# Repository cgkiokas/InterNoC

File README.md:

# InterNoC
InterNoC prototype board

### Description:
Nowadays, many embedded systems host a significant number of micro-controllers and processors (i.e. IoT devices, vehicles, airplanes, satellites) and as this number continues to increase, traditional bus solutions will start to fail on those platforms as well. Network-on-Chip (NoC) not only offer a scalable solution for MPSoC interconnects but they can also provide a uniform platform of communication to embedded systems with multiple interconnected devices.

This project aims to build an open-source FPGA-based NoC where devices can be connected to each other, transparently, enabling mixed protocol communication between multiple master / slave devices, without the need for a shared bus and at the same time allowing each device to operate in its own clock domain.

### Link to project page:
https://hackaday.io/project/27083-internoc

### Setup Notes:
All components are packed in InterNoC.lib & InterNoC.pretty so adding them in the component library and putting it in top priority should make the parts fully portable.

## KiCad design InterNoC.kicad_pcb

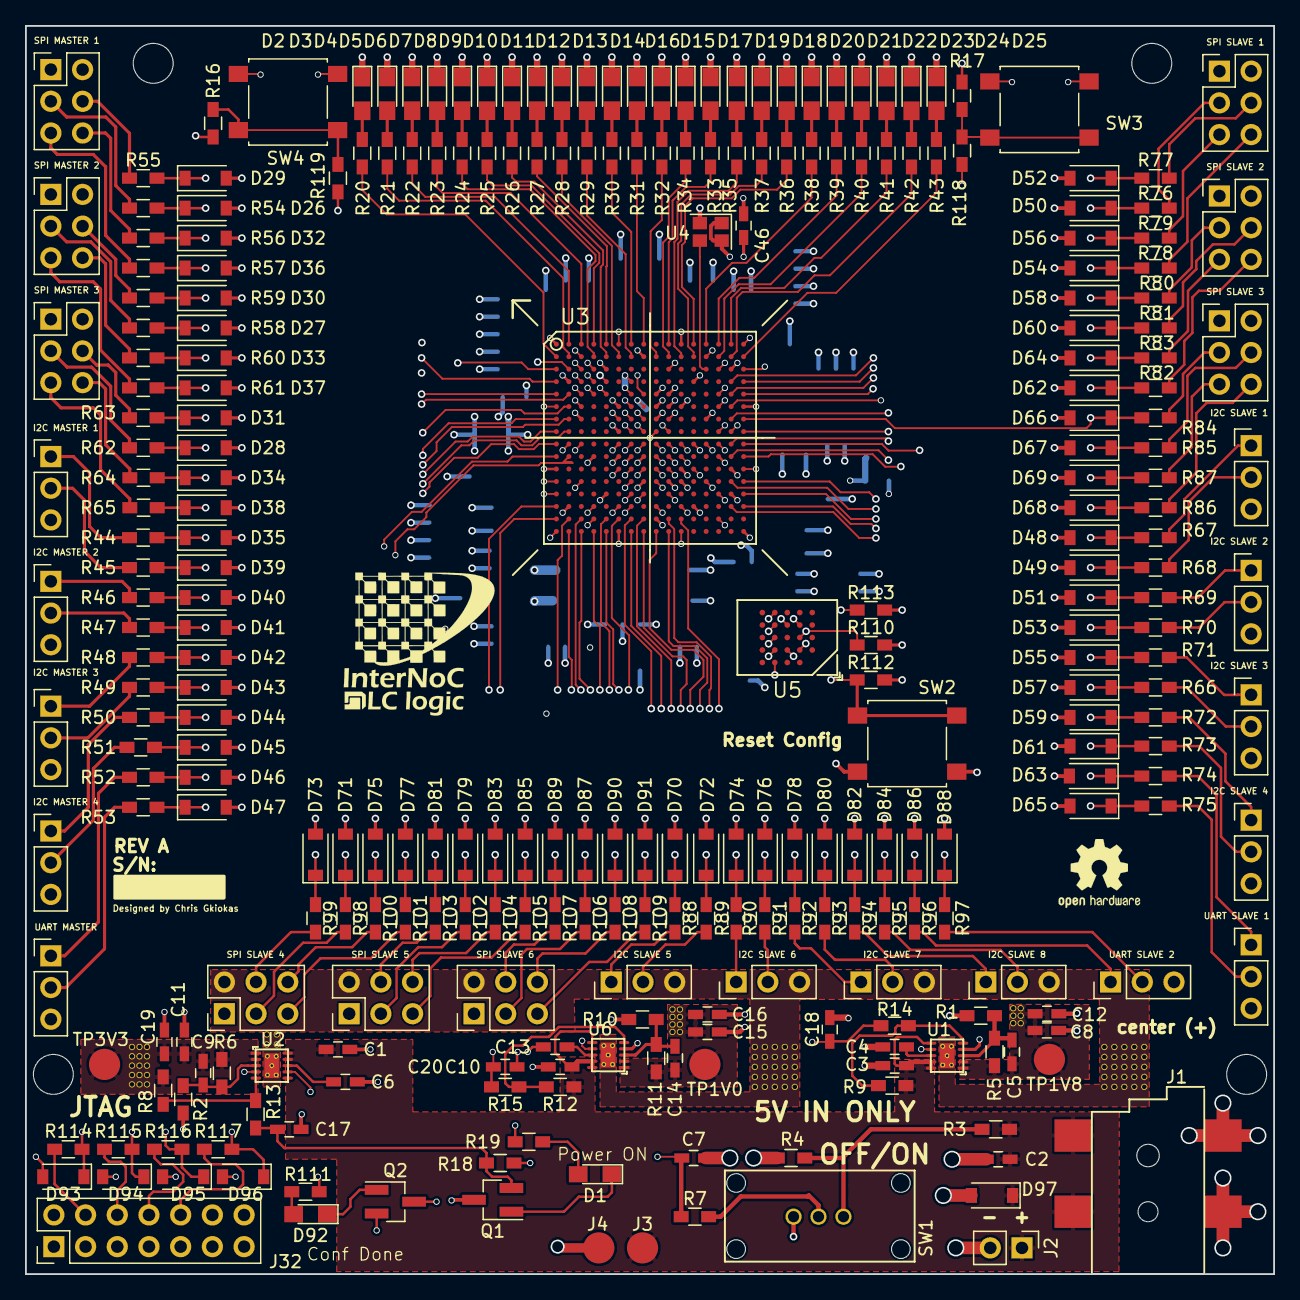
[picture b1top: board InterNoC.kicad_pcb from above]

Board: 6 copper layers, 100.0 x 100.0 mm, 345 parts (0 on the bottom side), 226 nets.

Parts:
C1, C3, C8, C10, C11, C15: 10uF X5R; C_0603_HandSoldering
C2: 10uF; C_0603_HandSoldering
C4, C6, C13: 0.1uF; C_0603_HandSoldering
C5, C9, C14, C114: 10nF X5R; C_0603_HandSoldering
C7, C46, C110: 100nF; C_0603_HandSoldering
C12, C16, C19: 100nF X5R; C_0603_HandSoldering
C17: 220nF; C_0603_HandSoldering
C18, C20: 680nF; C_0603_HandSoldering
C21, C22, C23, C24, C80: 100uF X5R; C_1210_HandSoldering
C25, C26, C27, C28, C29, C30, C31, C32, C83, C87, C91, C94: 4.7uF X5R; C_0805_HandSoldering
C33, C34, C35, C36, C37, C38, C39, C40, C41, C42, C43, C44, C45, C47, C48, C49, C85, C92, C95, C97, C98, C100, C104, C109: 470nF X5R; C_0603_HandSoldering
C50, C51, C52, C53, C54, C55, C56, C57, C89, C101, C105, C106, C108, C111, C113: 47nF X5R; C_0603_HandSoldering
C81, C86: 47uF X5R; C_1210_HandSoldering
C107: 47uF; C_1210_HandSoldering
C112: 470nF; C_0603_HandSoldering
D1, D2, D3, D4, D5, D6, D7, D8, D9, D10, D11, D12, D13, D14, D15, D16, D17, D18, D19, D20, D21, D22, D23, D24, D25, D92: LED; LED_0805_HandSoldering
D26, D27, D28, D29, D30, D31, D32, D33, D34, D35, D36, D37, D38, D39, D40, D41, D42, D43, D44, D45, D46, D47, D48, D49, D50, D51, D52, D53, D54, D55, D56, D57, D58, D59, D60, D61, D62, D63, D64, D65, D66, D67, D68, D69, D70, D71, D72, D73, D74, D75, D76, D77, D78, D79, D80, D81, D82, D83, D84, D85, D86, D87, D88, D89, D90, D91, D93, D94, D95, D96: 3.3v; D_SOD-123
D97: 6v; D_SOD-123
I2C MASTER 1: I2C_MASTER_1; Pin_Header_Straight_1x03_Pitch2.54mm
I2C MASTER 2: I2C_MASTER_2; Pin_Header_Straight_1x03_Pitch2.54mm
I2C MASTER 3: I2C_MASTER_3; Pin_Header_Straight_1x03_Pitch2.54mm
I2C MASTER 4: I2C_MASTER_4; Pin_Header_Straight_1x03_Pitch2.54mm
I2C SLAVE 1: I2C_SLAVE_1; Pin_Header_Straight_1x03_Pitch2.54mm
I2C SLAVE 2: I2C_SLAVE_2; Pin_Header_Straight_1x03_Pitch2.54mm
I2C SLAVE 3: I2C_SLAVE_3; Pin_Header_Straight_1x03_Pitch2.54mm
I2C SLAVE 4: I2C_SLAVE_4; Pin_Header_Straight_1x03_Pitch2.54mm
I2C SLAVE 5: I2C_SLAVE_5; Pin_Header_Straight_1x03_Pitch2.54mm
I2C SLAVE 6: I2C_SLAVE_6; Pin_Header_Straight_1x03_Pitch2.54mm
I2C SLAVE 7: I2C_SLAVE_7; Pin_Header_Straight_1x03_Pitch2.54mm
I2C SLAVE 8: I2C_SLAVE_8; Pin_Header_Straight_1x03_Pitch2.54mm
J1: BARREL_JACK; PJ-002AH-SMT-TR
J2: CONN_01X02; Pin_Header_Straight_1x02_Pitch2.54mm
J3: TEST_PW_IN; test_point_single
J4: TEST_GND; test_point_single
J32: JTAG HEADER; Pin_Header_Straight_2x07_Pitch2.54mm
L4, L5: 600Ohm/100Mhz; L_0805_HandSoldering
Q1: FDV301N; SOT-23_Handsoldering
Q2: Q_NMOS_DGS; SOT-23_Handsoldering
R1: 1.5K 1%; R_0603_HandSoldering
R2: 1.15K 1%; R_0603_HandSoldering
R3, R4, R7, R16, R17, R18, R118, R119: 10K; R_0603_HandSoldering
R5: 1.87K 1%; R_0603_HandSoldering
R6: 3.57K 1%; R_0603_HandSoldering
R8: 20K; R_0603_HandSoldering
R9, R12: 56K; R_0603_HandSoldering
R10: 10.2K 1%; R_0603_HandSoldering
R11: 2.55K 1%; R_0603_HandSoldering
R13, R14, R15: 4.7K; R_0603_HandSoldering
R19: 680R; R_0603_HandSoldering
R20, R21, R22, R23, R24, R25, R26, R27, R28, R29, R30, R31, R32, R33, R34, R35, R36, R37, R38, R39, R40, R41, R42, R43, R111: 330R; R_0603_HandSoldering
R44, R45, R46, R47, R48, R49, R50, R51, R52, R53, R54, R55, R56, R57, R58, R59, R60, R61, R62, R63, R64, R65, R66, R67, R68, R69, R70, R71, R72, R73, R74, R75, R76, R77, R78, R79, R80, R81, R82, R83, R84, R85, R86, R87, R88, R89, R90, R91, R92, R93, R94, R95, R96, R97, R98, R99, R100, R101, R102, R103, R104, R105, R106, R107, R108, R109, R114, R115, R116, R117: 200; R_0603_HandSoldering
R110, R112, R113: 4.7k; R_0603_HandSoldering
SPI MASTER 1: SPI_MASTER_1; Pin_Header_Straight_2x03_Pitch2.54mm
SPI MASTER 2: SPI_MASTER_2; Pin_Header_Straight_2x03_Pitch2.54mm
SPI MASTER 3: SPI_MASTER_3; Pin_Header_Straight_2x03_Pitch2.54mm
SPI SLAVE 1: SPI_SLAVE_1; Pin_Header_Straight_2x03_Pitch2.54mm
SPI SLAVE 2 : SPI_SLAVE_2; Pin_Header_Straight_2x03_Pitch2.54mm
SPI SLAVE 3: SPI_SLAVE_3; Pin_Header_Straight_2x03_Pitch2.54mm
SPI SLAVE 4: SPI_SLAVE_4; Pin_Header_Straight_2x03_Pitch2.54mm
SPI SLAVE 5: SPI_SLAVE_5; Pin_Header_Straight_2x03_Pitch2.54mm
SPI SLAVE 6: SPI_SLAVE_6; Pin_Header_Straight_2x03_Pitch2.54mm
SW1: SW_SPDT; MSS120004
SW2: RST_CONF; SW_SPST_B3S-1000
SW3, SW4: SW_Push; SW_SPST_B3S-1000
TP1V0: TEST_1V0; test_point_single
TP1V8: TEST_1V8; test_point_single
TP3V3: TEST_3V3; test_point_single
U1, U6: TPS7A9101DSKT
U2: TPS7A9201DSKR
U3: xc7a35tftg256; XC7A35T-1FTG256C
U4: ABRACON_ASDM1-100.000MHZ-LC-T; Crystal_SMD_2520-4pin_2.5x2.0mm
U5: S25FL128SAGBHIA00
UART MASTER : UART_MASTER_1; Pin_Header_Straight_1x03_Pitch2.54mm
UART SLAVE 1: UART_SLAVE_1; Pin_Header_Straight_1x03_Pitch2.54mm
UART SLAVE 2: UART_SLAVE_2; Pin_Header_Straight_1x03_Pitch2.54mm

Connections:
/Artix7/GNDADC: C114.2, L5.1, U3.G7, U3.H7, U3.H8, U3.J7, U3.J8
/Artix7/TCK: D94.1, R115.2, U3.L7
/Artix7/TDI: D96.1, R117.2, U3.N7
/Artix7/TDO: D95.1, R116.2, U3.N8
/Artix7/TMS: D93.1, R114.2, U3.M7
/Artix7/VCC1V0: C14.1, C15.1, C16.1, C80.1, C83.1, C87.1, C92.1, C95.1, C98.1, C101.1, C105.1, C107.1, C108.1, C112.1, C113.1, R11.1, TP1V0.1, U3.E10, U3.F7, U3.F9, U3.F11, U3.G6, U3.H9, U3.J6, U3.K9, U3.L8, U6.1, U6.2
/Artix7/VCC1V8: C5.1, C8.1, C12.1, C86.1, C91.1, C94.1, C97.1, C100.1, C104.1, C106.1, C111.1, L4.2, R5.1, TP1V8.1, U1.1, U1.2, U3.F8, U3.G10, U3.J10, U3.K11, U3.L10
/Artix7/VCC3V3: C9.1, C11.1, C19.1, C21.1, C22.1, C23.1, C24.1, C25.1, C26.1, C27.1, C28.1, C29.1, C30.1, C31.1, C32.1, C33.1, C34.1, C35.1, C36.1, C37.1, C38.1, C39.1, C40.1, C41.1, C42.1, C43.1, C44.1, C45.1, C46.1, C47.1, C48.1, C49.1, C50.1, C51.1, C52.1, C53.1, C54.1, C55.1, C56.1, C57.1, C81.1, C85.1, C89.1, C110.1, J32.2, R6.1, R8.2, R18.2, R19.2, R110.1, R111.1, R112.1, R113.1, SW3.1, SW4.1, TP3V3.1, U2.1, U2.2, U3.A6, U3.A16, U3.B3, U3.B13, U3.C10, U3.D7, U3.E4, U3.E7, U3.E14, U3.F1, U3.H15, U3.J2, U3.J12, U3.L6, U3.L16, U3.M3, U3.M9, U3.M13, U3.N10, U3.P7, U3.R4, U3.R14, U3.T1, U3.T11, U4.1, U4.4, U5.A4, U5.B4, U5.C4, U5.D4, U5.E4
/Artix7/VCCADC: C109.1, C114.1, L4.1, U3.G8
/PowerSupply/PGOOD: C17.1, Q1.2, R13.2, R18.1
/PowerSupply/PGOOD1V0: C20.1, R15.2, U1.7
/PowerSupply/PGOOD1V8: C18.1, R14.2, U2.7
/PowerSupply/PWR_IN: C1.1, C2.1, C3.1, C10.1, D97.1, J1.1, J2.1, J3.1, R3.1, R9.2, R12.2, U1.6, U1.9, U1.10, U2.6, U2.9, U2.10, U6.6, U6.9, U6.10
CLOCK: U3.C13, U4.3
GND: C1.2, C2.2, C3.2, C4.2, C6.2, C7.2, C8.2, C10.2, C11.2, C12.2, C13.2, C15.2, C16.2, C17.2, C18.2, C19.2, C20.2, C21.2, C22.2, C23.2, C24.2, C25.2, C26.2, C27.2, C28.2, C29.2, C30.2, C31.2, C32.2, C33.2, C34.2, C35.2, C36.2, C37.2, C38.2, C39.2, C40.2, C41.2, C42.2, C43.2, C44.2, C45.2, C46.2, C47.2, C48.2, C49.2, C50.2, C51.2, C52.2, C53.2, C54.2, C55.2, C56.2, C57.2, C80.2, C81.2, C83.2, C85.2, C86.2, C87.2, C89.2, C91.2, C92.2, C94.2, C95.2, C97.2, C98.2, C100.2, C101.2, C104.2, C105.2, C106.2, C107.2, C108.2, C109.2, C110.2, C111.2, C112.2, C113.2, D2.1, D3.1, D4.1, D5.1, D6.1, D7.1, D8.1, D9.1, D10.1, D11.1, D12.1, D13.1, D14.1, D15.1, D16.1, D17.1, D18.1, D19.1, D20.1, D21.1, D22.1, D23.1, D24.1, D25.1, D26.2, D27.2, D28.2, D29.2, D30.2, D31.2, D32.2, D33.2, D34.2, D35.2, D36.2, D37.2, D38.2, D39.2, D40.2, D41.2, D42.2, D43.2, D44.2, D45.2, D46.2, D47.2, D48.2, D49.2, D50.2, D51.2, D52.2, D53.2, D54.2, D55.2, D56.2, D57.2, D58.2, D59.2, D60.2, D61.2, D62.2, D63.2, D64.2, D65.2, D66.2, D67.2, D68.2, D69.2, D70.2, D71.2, D72.2, D73.2, D74.2, D75.2, D76.2, D77.2, D78.2, D79.2, D80.2, D81.2, D82.2, D83.2, D84.2, D85.2, D86.2, D87.2, D88.2, D89.2, D90.2, D91.2, D93.2, D94.2, D95.2, D96.2, D97.2, I2C MASTER 1.3, I2C MASTER 2.3, I2C MASTER 3.3, I2C MASTER 4.3, I2C SLAVE 1.3, I2C SLAVE 2.3, I2C SLAVE 3.3, I2C SLAVE 4.3, I2C SLAVE 5.3, I2C SLAVE 6.3, I2C SLAVE 7.3, I2C SLAVE 8.3, J1.2, J1.3, J2.2, J4.1, J32.1, J32.3, J32.5, J32.7, J32.9, J32.11, J32.13, L5.2, Q1.3, Q2.3, R1.1, R2.1, R4.2, R10.1, R16.1, R17.1, SPI MASTER 1.2, SPI MASTER 2.2, SPI MASTER 3.2, SPI SLAVE 1.2, SPI SLAVE 2.2, SPI SLAVE 3.2, SPI SLAVE 4.2, SPI SLAVE 5.2, SPI SLAVE 6.2, SW1.1, SW2.2, U1.4, U1.11, U2.4, U2.11, U3.A1, U3.A11, U3.B8, U3.C5, U3.C15, U3.D2, U3.D12, U3.E9, U3.F6, U3.F10, U3.F16, U3.G3, U3.G9, U3.G13, U3.H6, U3.J9, U3.J11, U3.K4, U3.K6, U3.K7, U3.K8, U3.K14, U3.L1, U3.L11, U3.L15, U3.M8, U3.M10, U3.M11, U3.N5, U3.N15, U3.P2, U3.P12, U3.R9, U3.T6, U3.T16, U4.2, U5.B3, U6.4, U6.11, UART MASTER.3, UART SLAVE 1.3, UART SLAVE 2.3
GP_BTN_1: R118.1, U3.M1
GP_BTN_2: R119.1, U3.N1
I2C_MASTER_1_SCL: D39.1, R45.2, U3.F3
I2C_MASTER_1_SDA: D35.1, R44.2, U3.F2
I2C_MASTER_2_SCL: D41.1, R47.2, U3.G2
I2C_MASTER_2_SDA: D40.1, R46.2, U3.G1
I2C_MASTER_3_SCL: D43.1, R49.2, U3.H2
I2C_MASTER_3_SDA: D42.1, R48.2, U3.H1
I2C_MASTER_4_SCL: D45.1, R51.2, U3.J3
I2C_MASTER_4_SDA: D44.1, R50.2, U3.J1
I2C_SLAVE_1_SCL: D49.1, R68.1, U3.J15
I2C_SLAVE_1_SDA: D48.1, R67.1, U3.J16
I2C_SLAVE_2_SCL: D53.1, R70.1, U3.K15
I2C_SLAVE_2_SDA: D51.1, R69.1, U3.K16
I2C_SLAVE_3_SCL: D57.1, R66.1, U3.M15
I2C_SLAVE_3_SDA: D55.1, R71.1, U3.M16
I2C_SLAVE_4_SCL: D61.1, R73.1, U3.N14
I2C_SLAVE_4_SDA: D59.1, R72.1, U3.N16
I2C_SLAVE_5_SCL: D72.1, R89.1, U3.R7
I2C_SLAVE_5_SDA: D70.1, R88.1, U3.T7
I2C_SLAVE_6_SCL: D76.1, R91.1, U3.R8
I2C_SLAVE_6_SDA: D74.1, R90.1, U3.T8
I2C_SLAVE_7_SCL: D80.1, R93.1, U3.P9
I2C_SLAVE_7_SDA: D78.1, R92.1, U3.T9
I2C_SLAVE_8_SCL: D84.1, R95.1, U3.R10
I2C_SLAVE_8_SDA: D82.1, R94.1, U3.T10
LED_1: R20.1, U3.B1
LED_2: R21.1, U3.B2
LED_3: R22.1, U3.A2
LED_4: R23.1, U3.A3
LED_5: R24.1, U3.B4
LED_6: R25.1, U3.A4
LED_7: R26.1, U3.B5
LED_8: R27.1, U3.A5
LED_9: R28.1, U3.B6
LED_10: R29.1, U3.B7
LED_11: R30.1, U3.A7
LED_12: R31.1, U3.A8
LED_13: R32.1, U3.B9
LED_14: R33.1, U3.A10
LED_15: R34.1, U3.B10
LED_16: R35.1, U3.B11
LED_17: R36.1, U3.A12
LED_18: R37.1, U3.B12
LED_19: R38.1, U3.A13
LED_20: R39.1, U3.A14
LED_21: R40.1, U3.B14
LED_22: R41.1, U3.A15
LED_23: R42.1, U3.B15
LED_24: R43.1, U3.B16
unnamed: C4.1, U1.8
unnamed: C5.2, R1.2, R5.2, U1.3
unnamed: C6.1, U2.8
unnamed: C7.1, R7.1, U6.7
unnamed: C9.2, R2.2, R6.2, U2.3
unnamed: C13.1, U6.8
unnamed: C14.2, R10.2, R11.2, U6.3
unnamed: D1.1, Q1.1
unnamed: D1.2, R19.1
unnamed: D2.2, R20.2
unnamed: D3.2, R21.2
unnamed: D4.2, R22.2
unnamed: D5.2, R23.2
unnamed: D6.2, R24.2
unnamed: D7.2, R25.2
unnamed: D8.2, R26.2
unnamed: D9.2, R27.2
unnamed: D10.2, R28.2
unnamed: D11.2, R29.2
unnamed: D12.2, R30.2
unnamed: D13.2, R31.2
unnamed: D14.2, R32.2
unnamed: D15.2, R33.2
unnamed: D16.2, R34.2
unnamed: D17.2, R35.2
unnamed: D18.2, R36.2
unnamed: D19.2, R37.2
unnamed: D20.2, R38.2
unnamed: D21.2, R39.2
unnamed: D22.2, R40.2
unnamed: D23.2, R41.2
unnamed: D24.2, R42.2
unnamed: D25.2, R43.2
unnamed: D92.1, Q2.1
unnamed: D92.2, R111.2
unnamed: I2C MASTER 1.1, R44.1
unnamed: I2C MASTER 1.2, R45.1
unnamed: I2C MASTER 2.1, R46.1
unnamed: I2C MASTER 2.2, R47.1
unnamed: I2C MASTER 3.1, R48.1
unnamed: I2C MASTER 3.2, R49.1
unnamed: I2C MASTER 4.1, R50.1
unnamed: I2C MASTER 4.2, R51.1
unnamed: R52.1, UART MASTER.1
unnamed: R53.1, UART MASTER.2
unnamed: R54.1, SPI MASTER 1.3
unnamed: R55.1, SPI MASTER 1.4
unnamed: R57.1, SPI MASTER 1.5
unnamed: R56.1, SPI MASTER 1.6
unnamed: R58.1, SPI MASTER 2.3
unnamed: R59.1, SPI MASTER 2.4
unnamed: R61.1, SPI MASTER 2.5
unnamed: R60.1, SPI MASTER 2.6
unnamed: R62.1, SPI MASTER 3.3
unnamed: R63.1, SPI MASTER 3.4
unnamed: R65.1, SPI MASTER 3.5
unnamed: R64.1, SPI MASTER 3.6
unnamed: I2C SLAVE 1.1, R67.2
unnamed: I2C SLAVE 1.2, R68.2
unnamed: I2C SLAVE 2.1, R69.2
unnamed: I2C SLAVE 2.2, R70.2
unnamed: I2C SLAVE 3.1, R71.2
unnamed: I2C SLAVE 3.2, R66.2
unnamed: I2C SLAVE 4.1, R72.2
unnamed: I2C SLAVE 4.2, R73.2
unnamed: R74.2, UART SLAVE 1.1
unnamed: R75.2, UART SLAVE 1.2
unnamed: R76.2, SPI SLAVE 1.3
unnamed: R77.2, SPI SLAVE 1.4
unnamed: R79.2, SPI SLAVE 1.5
unnamed: R78.2, SPI SLAVE 1.6
unnamed: R80.2, SPI SLAVE 2.3
unnamed: R81.2, SPI SLAVE 2.4
unnamed: R83.2, SPI SLAVE 2.5
unnamed: R82.2, SPI SLAVE 2.6
unnamed: R84.2, SPI SLAVE 3.3
unnamed: R85.2, SPI SLAVE 3.4
unnamed: R87.2, SPI SLAVE 3.5
unnamed: R86.2, SPI SLAVE 3.6
unnamed: I2C SLAVE 5.1, R88.2
unnamed: I2C SLAVE 5.2, R89.2
unnamed: I2C SLAVE 6.1, R90.2
unnamed: I2C SLAVE 6.2, R91.2
unnamed: I2C SLAVE 7.1, R92.2
unnamed: I2C SLAVE 7.2, R93.2
unnamed: I2C SLAVE 8.1, R94.2
unnamed: I2C SLAVE 8.2, R95.2
unnamed: R96.2, UART SLAVE 2.1
unnamed: R97.2, UART SLAVE 2.2
unnamed: R98.2, SPI SLAVE 4.3
unnamed: R99.2, SPI SLAVE 4.4
unnamed: R101.2, SPI SLAVE 4.5
unnamed: R100.2, SPI SLAVE 4.6
unnamed: R102.2, SPI SLAVE 5.3
unnamed: R103.2, SPI SLAVE 5.4
unnamed: R105.2, SPI SLAVE 5.5
unnamed: R104.2, SPI SLAVE 5.6
unnamed: R106.2, SPI SLAVE 6.3
unnamed: R107.2, SPI SLAVE 6.4
unnamed: R109.2, SPI SLAVE 6.5
unnamed: R108.2, SPI SLAVE 6.6
unnamed: J32.4, R114.1
unnamed: J32.6, R115.1
unnamed: J32.8, R116.1
unnamed: J32.10, R117.1
unnamed: Q2.2, U3.H10
unnamed: R3.2, R4.1, SW1.3
unnamed: R7.2, SW1.2
unnamed: R12.1, R15.1, U6.5
unnamed: R8.1, R13.1, U2.5
unnamed: R9.1, R14.1, U1.5
unnamed: R110.2, U3.L12, U5.C2
unnamed: R112.2, SW2.1, U3.L9
unnamed: R113.2, U3.K10
unnamed: R17.2, R118.2, SW3.2
unnamed: R16.2, R119.2, SW4.2
unnamed: U3.E8, U5.B2
unnamed: U3.J13, U5.D3
unnamed: U3.J14, U5.D2
SPI_MASTER_1_CS: D36.1, R57.2, U3.C1
SPI_MASTER_1_MISO: D32.1, R56.2, U3.C2
SPI_MASTER_1_MOSI: D29.1, R55.2, U3.C4
SPI_MASTER_1_SCLK: D26.1, R54.2, U3.C3
SPI_MASTER_2_CS: D37.1, R61.2, U3.D5
SPI_MASTER_2_MISO: D33.1, R60.2, U3.D1
SPI_MASTER_2_MOSI: D30.1, R59.2, U3.D3
SPI_MASTER_2_SCLK: D27.1, R58.2, U3.D4
SPI_MASTER_3_CS: D38.1, R65.2, U3.E5
SPI_MASTER_3_MISO: D34.1, R64.2, U3.E3
SPI_MASTER_3_MOSI: D31.1, R63.2, U3.E1
SPI_MASTER_3_SCLK: D28.1, R62.2, U3.E2
SPI_SLAVE_1_CS: D56.1, R79.1, U3.D15
SPI_SLAVE_1_MISO: D54.1, R78.1, U3.D16
SPI_SLAVE_1_MOSI: D52.1, R77.1, U3.C14
SPI_SLAVE_1_SCLK: D50.1, R76.1, U3.C16
SPI_SLAVE_2_CS: D64.1, R83.1, U3.F14
SPI_SLAVE_2_MISO: D62.1, R82.1, U3.F15
SPI_SLAVE_2_MOSI: D60.1, R81.1, U3.E16
SPI_SLAVE_2_SCLK: D58.1, R80.1, U3.E15
SPI_SLAVE_3_CS: D69.1, R87.1, U3.H16
SPI_SLAVE_3_MISO: D68.1, R86.1, U3.H14
SPI_SLAVE_3_MOSI: D67.1, R85.1, U3.G15
SPI_SLAVE_3_SCLK: D66.1, R84.1, U3.G16
SPI_SLAVE_4_CS: D77.1, R101.1, U3.T2
SPI_SLAVE_4_MISO: D75.1, R100.1, U3.R2
SPI_SLAVE_4_MOSI: D73.1, R99.1, U3.R1
SPI_SLAVE_4_SCLK: D71.1, R98.1, U3.P1
SPI_SLAVE_5_CS: D85.1, R105.1, U3.T4
SPI_SLAVE_5_MISO: D83.1, R104.1, U3.P4
SPI_SLAVE_5_MOSI: D81.1, R103.1, U3.T3
SPI_SLAVE_5_SCLK: D79.1, R102.1, U3.R3
SPI_SLAVE_6_CS: D91.1, R109.1, U3.P6
SPI_SLAVE_6_MISO: D90.1, R108.1, U3.R6
SPI_SLAVE_6_MOSI: D89.1, R107.1, U3.T5
SPI_SLAVE_6_SCLK: D87.1, R106.1, U3.R5
UART_MASTER_1_RX: D47.1, R53.2, U3.K2
UART_MASTER_1_TX: D46.1, R52.2, U3.K1
UART_SLAVE_1_RX: D65.1, R75.1, U3.P15
UART_SLAVE_1_TX: D63.1, R74.1, U3.P16
UART_SLAVE_2_RX: D88.1, R97.1, U3.P11
UART_SLAVE_2_TX: D86.1, R96.1, U3.R11

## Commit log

2017-09-16 hackaday link add
2017-09-21 schematic ready commit
    first completed schematic commit
2017-09-25 Altered power supply from switcher to ldo's
2017-09-28 before layout commit
2017-09-28 comt
2017-10-02 fixed spi loc
2017-10-02 linguistfix
2017-10-07 pcb complete commit
    the layout is complete. NOT checked & verified
2017-10-10 layout finalizing
    drc complete
2017-10-23 fixes
